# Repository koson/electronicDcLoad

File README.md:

# electronicDcLoad
A simple DC Electronic Load using an Arduino Nano (0-50V/0-5A)

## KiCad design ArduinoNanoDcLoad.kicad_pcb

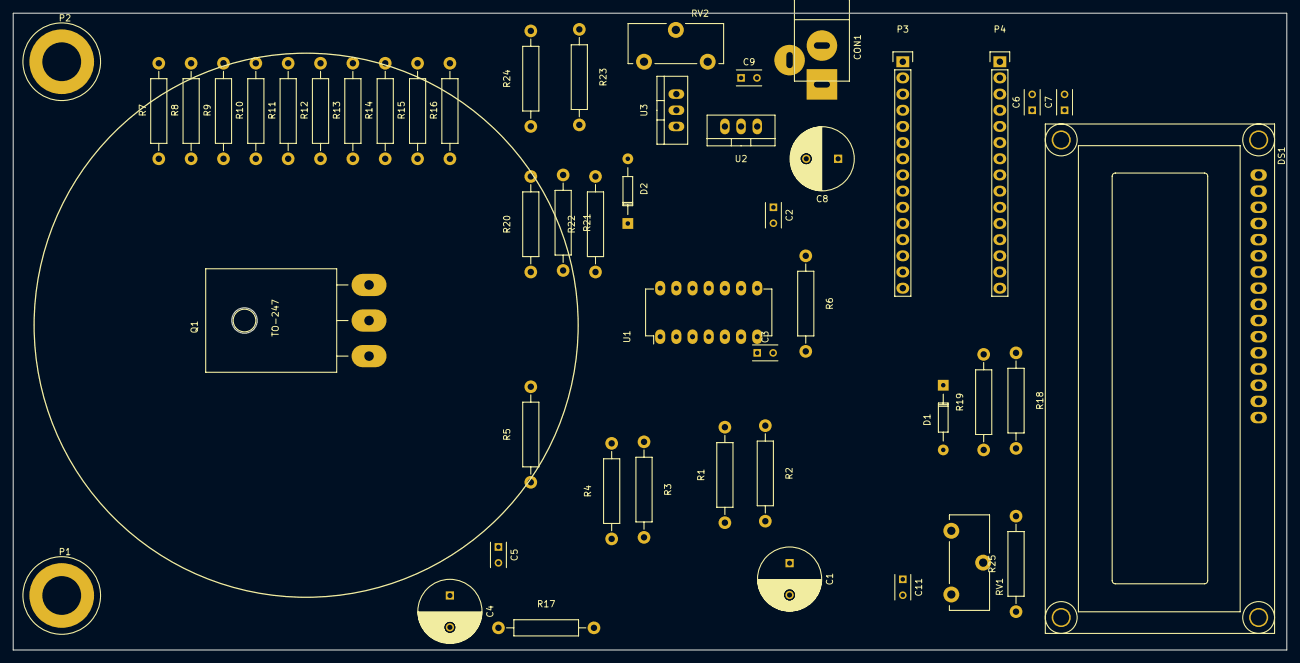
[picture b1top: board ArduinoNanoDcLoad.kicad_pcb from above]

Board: 2 copper layers, 200.0 x 100.0 mm, 49 parts (0 on the bottom side), 30 nets, no tracks yet.

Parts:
C1: 100μ; C_Radial_D10_L20_P5
C2, C5, C6, C7, C9, C11: 100n; C_Rect_L4_W2.5_P2.5
C3: 10n; C_Rect_L4_W2.5_P2.5
C4: 10µ; C_Radial_D10_L20_P5
C8: 220µ; C_Radial_D10_L20_P5
CON1: BARREL_JACK; JACK_ALIM
D1, D2: 5,1V; Diode_DO-35_SOD27_Horizontal_RM10
DS1: LCD16X2; WC1602A
P1: DCLOAD+; Banana_Jack_1Pin
P2: DCLOAD-; Banana_Jack_1Pin
P3, P4: CONN_01X15; Pin_Header_Straight_1x15
Q1: IRFP250N; TO-247_Horizontal_Neutral123_largePads
R1, R2: 100k; Resistor_Horizontal_RM15mm
R3, R18, R21: 18k; Resistor_Horizontal_RM15mm
R4, R19, R20, R23: 2k; Resistor_Horizontal_RM15mm
R5, R25: 470; Resistor_Horizontal_RM15mm
R6, R22: 1k; Resistor_Horizontal_RM15mm
R7, R8, R9, R10, R11, R12, R13, R14, R15, R16: 1; Resistor_Horizontal_RM15mm
R17: 10; Resistor_Horizontal_RM15mm
R24: 680; Resistor_Horizontal_RM15mm
RV1: 10k; Potentiometer_Trimmer-Piher-PT15-h5_vertical
RV2: 200; Potentiometer_Trimmer-Piher-PT15-h5_vertical
U1: LMC6484; DIP-14_W7.62mm_LongPads
U2: LM7812; TO-220_Neutral123_Vertical
U3: LM317T; TO-220_Neutral123_Vertical

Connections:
+5V: C11.2, DS1.2, P4.4, R24.2, R25.1, RV1.3, U3.2
+12V: C9.1, U1.4, U2.3, U3.3
/ADC6: C7.1, D2.1, P4.6, R22.1
/ADC7: C6.1, D1.1, P4.5, R18.1, R19.2
/AIN0/PD6: DS1.13, P3.9
/AIN1/PD7: DS1.14, P3.10
/CLKO/PB0: DS1.4, P3.11
/OC1B/PB2: DS1.6, P3.13
/RESET/PC6: P3.3, P4.3
/T0/PD4: DS1.11, P3.7
/T1/PD5: DS1.12, P3.8
GND: C1.2, C2.2, C5.2, C6.2, C7.2, D1.2, D2.2, DS1.1, DS1.16, P2.1, P3.4, P4.2, R4.2, R7.2, R8.2, R9.2, R10.2, R11.2, R12.2, R13.2, R14.2, R15.2, R16.2, R17.2, R19.1, R20.2, RV1.1, U1.11
unnamed: C1.1, R1.1, R2.2
unnamed: C2.1, R2.1, U1.3
unnamed: C3.1, R5.2, U1.7
unnamed: C3.2, R6.2, U1.6
unnamed: C4.1, C5.1, P1.1, Q1.2, R18.2
unnamed: C4.2, R17.1
unnamed: C8.1, CON1.1, U2.1
unnamed: C8.2, C9.2, C11.1, CON1.2, CON1.3, R23.2, U2.2
unnamed: DS1.3, RV1.2
unnamed: DS1.15, R25.2
unnamed: Q1.1, R5.1
unnamed: Q1.3, R6.1, R7.1, R8.1, R9.1, R10.1, R11.1, R12.1, R13.1, R14.1, R15.1, R16.1, U1.12
unnamed: R3.1, U1.1, U1.2
unnamed: R3.2, R4.1, U1.5
unnamed: R20.1, R21.2, U1.13
unnamed: R21.1, R22.2, U1.14
unnamed: R23.1, RV2.2
unnamed: R24.1, RV2.1, U3.1

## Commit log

2016-11-25 * added Kicad draft schematic
2016-11-27 * updated schematic
2016-11-27 * added netlist and pcb backup file and ArduinoNanoDcLoad.xml
2016-11-28 * updated
2016-11-29 * added basic power supply * added LCD
2016-11-29 added comment to schematic
2016-11-30 * updated pcb layout
2016-12-02 * update
2016-12-05 * added Arduino PWM 16 bit test sketch
2021-05-29 ียกฟะำ
